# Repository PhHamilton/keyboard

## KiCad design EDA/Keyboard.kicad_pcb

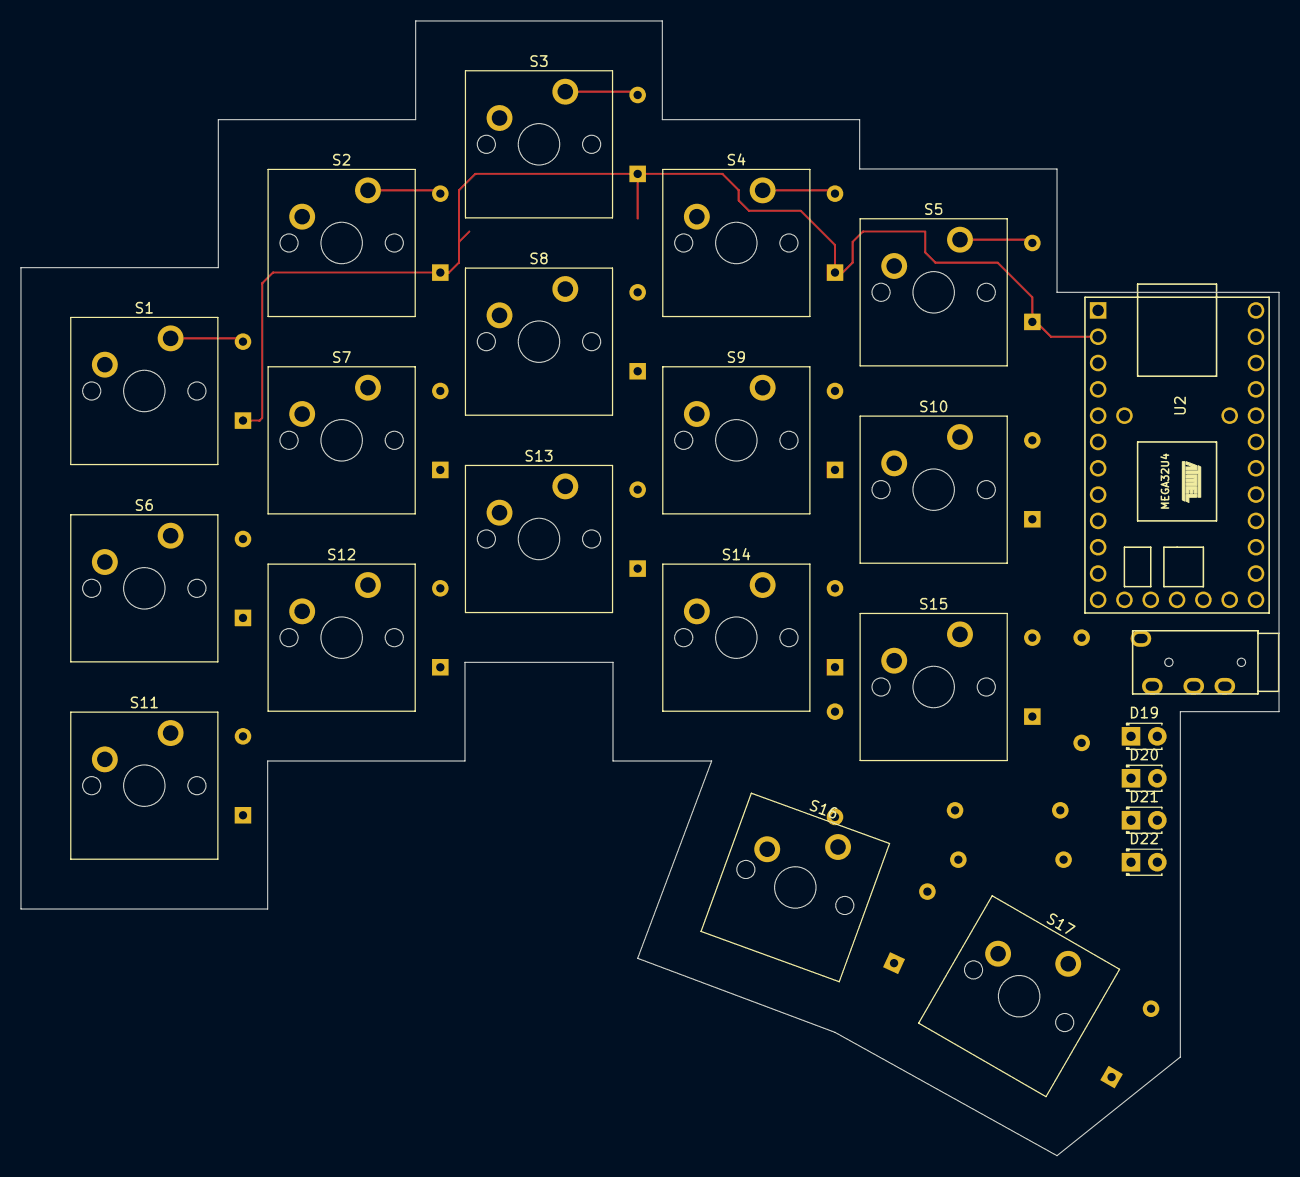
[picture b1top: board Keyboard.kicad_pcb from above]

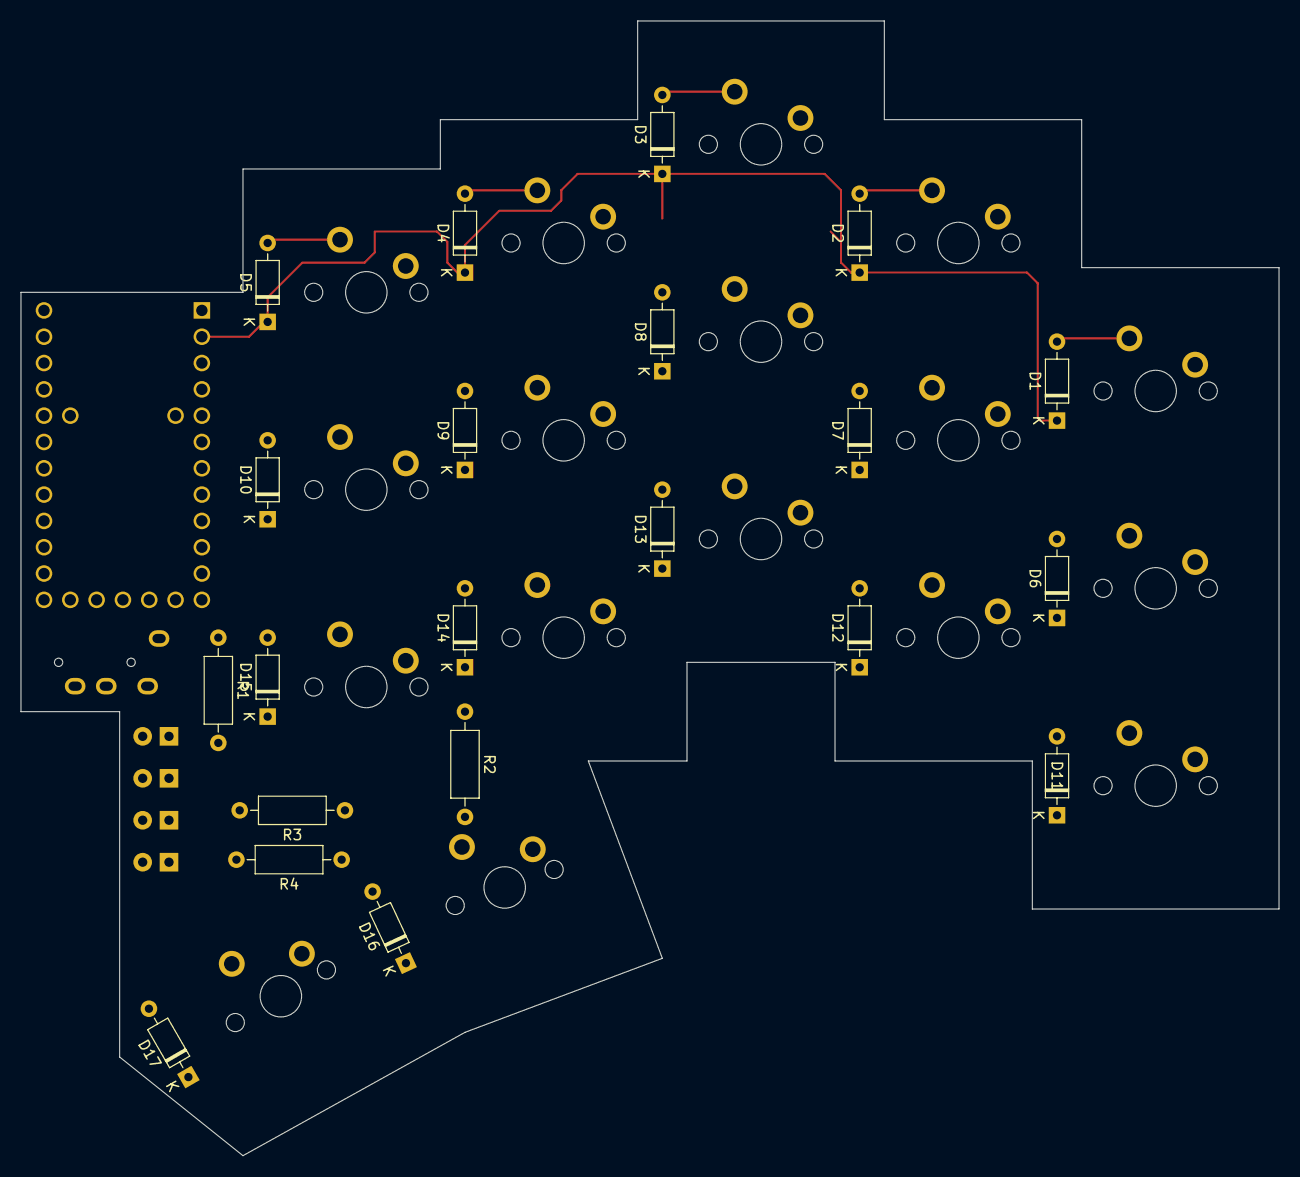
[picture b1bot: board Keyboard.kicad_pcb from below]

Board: 2 copper layers, 121.4 x 109.5 mm, 44 parts (21 on the bottom side), 36 nets.

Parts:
D1, D2, D3, D4, D5, D6, D7, D8, D9, D10, D11, D12, D13, D14, D15, D16, D17: Diode; Diode_DO-35
D19, D20, D21, D22: LED; LED_D1.8mm_W3.3mm_H2.4mm
R1, R2, R3, R4: Resistor; R_Axial_DIN0207_L6.3mm_D2.5mm_P10.16mm_Horizontal
S1, S2, S3, S4, S5, S6, S7, S8, S9, S10, S11, S12, S13, S14, S15, S16, S17: Keyswitch; MX_PCB_1.00u
U1: TRRS; TRRS_PJ-320A
U2: Teensy2.0_(C); Teensy2.0

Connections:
COL1: S1.1, S6.1, S11.1, U2.28 (PF0_ADC0)
COL2: S2.1, S7.1, S12.1, U2.27 (PF1_ADC1)
COL3: S3.1, S8.1, S13.1, S16.1, U2.26 (PF4_ADC4)
COL4: S4.1, S9.1, S14.1, S17.1, U2.25 (PF5_ADC5)
GND: R1.1, R2.1, R3.1, R4.1, U1.1 (SLEEVE), U2.1 (GND), U2.15 (GND)
LED1: D19.2 (A), U2.11 (PC6_OC3A_OC4A)
LED2: D20.2 (A), U2.12 (PC7_ICP3_OC4A)
unnamed: D1.2 (A), S1.2
unnamed: D2.2 (A), S2.2
unnamed: D3.2 (A), S3.2
unnamed: D4.2 (A), S4.2
unnamed: D5.2 (A), S5.2
unnamed: D6.2 (A), S6.2
unnamed: D7.2 (A), S7.2
unnamed: D8.2 (A), S8.2
unnamed: D9.2 (A), S9.2
unnamed: D10.2 (A), S10.2
unnamed: D11.2 (A), S11.2
unnamed: D12.2 (A), S12.2
unnamed: D13.2 (A), S13.2
unnamed: D14.2 (A), S14.2
unnamed: D15.2 (A), S15.2
unnamed: D16.2 (A), S16.2
unnamed: D17.2 (A), S17.2
unnamed: D19.1 (K), R1.2
unnamed: D20.1 (K), R2.2
unnamed: D21.1 (K), R3.2
unnamed: D22.1 (K), R4.2
RO5: S5.1, S10.1, S15.1
ROW1: D1.1 (K), D2.1 (K), D3.1 (K), D4.1 (K), D5.1 (K), U2.2 (PB0_SS)
ROW2: D6.1 (K), D7.1 (K), D8.1 (K), D9.1 (K), D10.1 (K), U2.3 (PB1_SCLK)
ROW3: D11.1 (K), D12.1 (K), D13.1 (K), D14.1 (K), D15.1 (K), U2.4 (PB2_MOSI)
ROW4: D16.1 (K), D17.1 (K), U2.5 (PB3_MISO)
SCL: U1.3 (RING1), U2.7 (PD0_INT0_SCL_OC0B)
SDA: U1.4 (RING2), U2.8 (PD1_INT1_SDA)
VCC: U1.2 (TIP), U2.14 (VCC)

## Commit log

2024-04-05 Removed cache
2024-04-05 Added .gitignore
2024-04-06 Added some basic files
2024-04-06 Fixed makefile, possible to make test and out
2024-04-06 Added some files
2024-04-06 Updated files after cache
2024-04-06 fixed small error in acutest
2024-04-06 Added some initial tests
2024-04-06 Added extra flag when testing
2024-04-06 Added some error codes
2024-04-06 Added keymap
2024-04-06 Commit to move to another computer, minor changes, names and some implementation
